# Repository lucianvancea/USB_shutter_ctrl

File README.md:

# Hardware shutter control for astrophotography 

## Intro
* Done in KiCad 
* Tested with [NINA]( https://nighttime-imaging.eu/ ) and Nikon D7000
* Works with this cable [ZWO ASIAIR N3]( https://astronomy-imaging-camera.com/product/zwo-shutter-release-cable-for-asiair-pro )
* [Video of board being soldered]( https://www.youtube.com/watch?v=h37NhTkAf3A&t)
* Uses RTS signal from an USB to UART bridge to control shutter release (and exposure time)

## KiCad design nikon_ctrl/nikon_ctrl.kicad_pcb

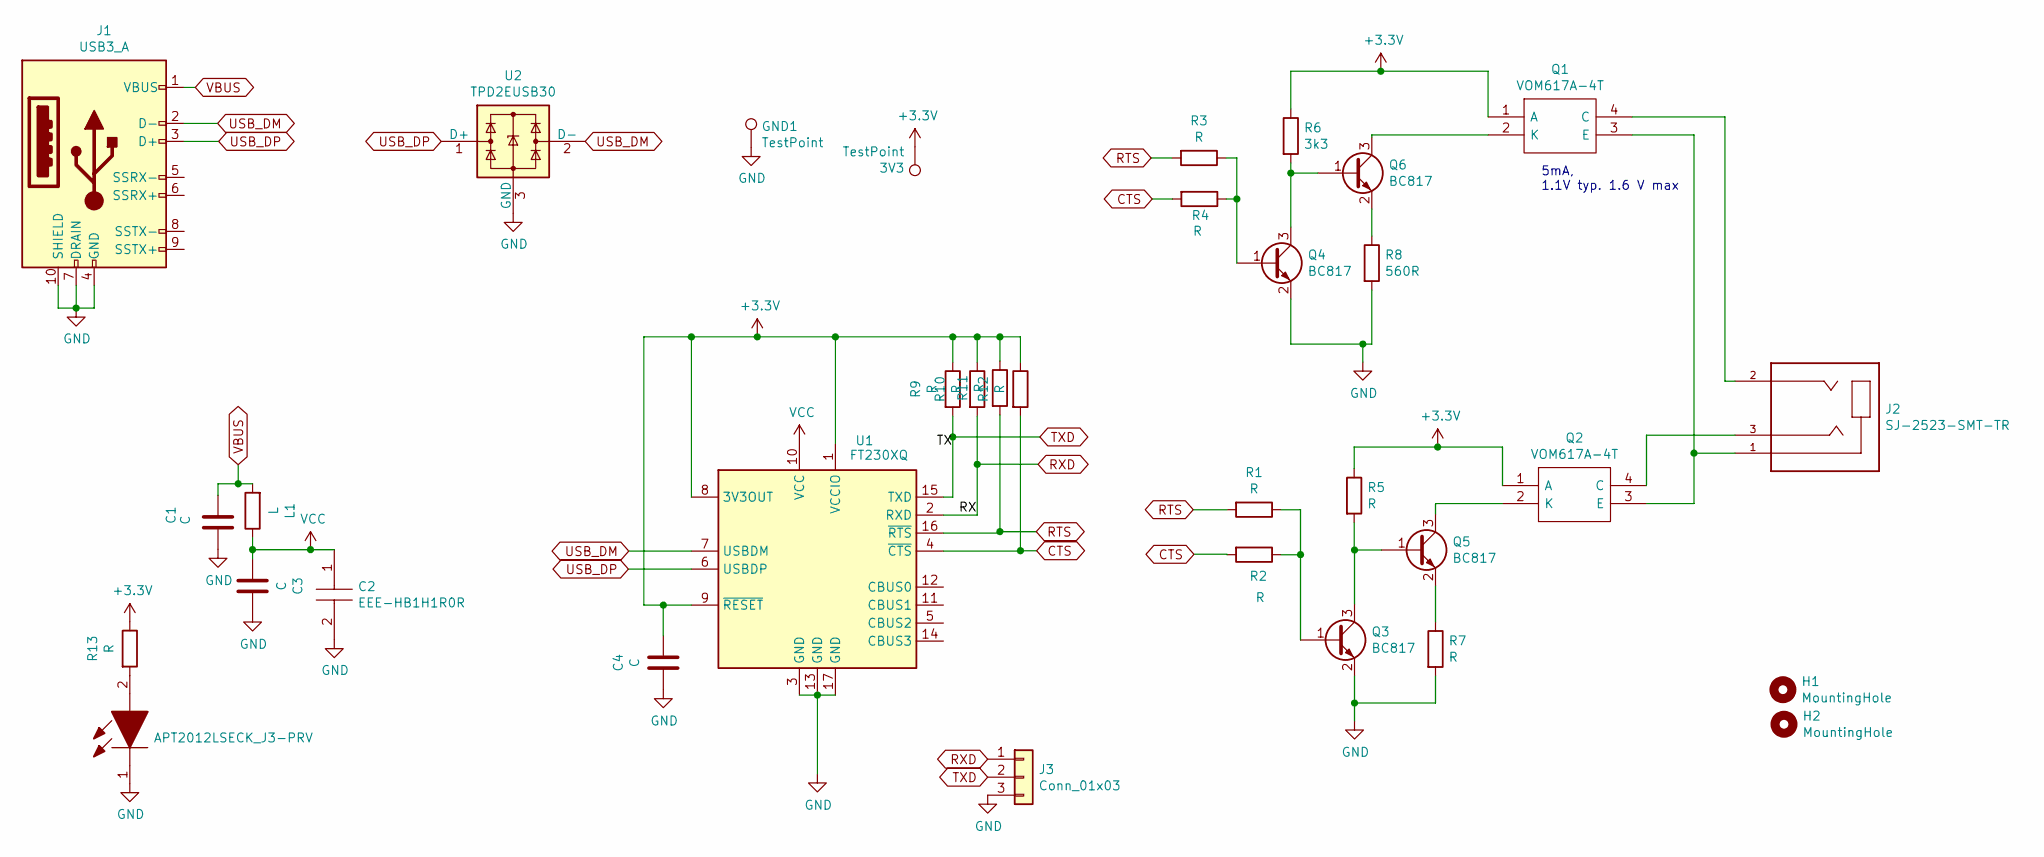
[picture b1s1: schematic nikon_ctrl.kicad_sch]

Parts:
3V3: TestPoint; TestPoint_Pad_D1.5mm
C1, C3, C4: C; C_0805_2012Metric
C2: EEE-HB1H1R0R; CAPAE430X610N; Mouser Part Number 667-EEE-HB1H1R0R
GND1: TestPoint; TestPoint_Pad_D1.5mm
H1, H2: MountingHole; MountingHole_2.2mm_M2_ISO7380_Pad
J1: USB3_A; USB3_A_Plug_Wuerth_692112030100_Horizontal
J2: SJ-2523-SMT-TR; CUI_SJ-2523-SMT-TR
J3: Conn_01x03; PinHeader_1x03_P2.54mm_Vertical
L1: L; R_0805_2012Metric_Pad1.15x1.40mm_HandSolder
LED1: APT2012LSECK_J3-PRV; LEDC2012X75N; Mouser Part Number 604-APT2012LSECKJ3RV
Q1, Q2: VOM617A-4T; VOM617A8X001T; Mouser Part Number 78-VOM617A-4T
Q3, Q4, Q5, Q6: BC817; SOT-23
R1, R2, R3, R4, R5, R7, R9, R10, R11, R12, R13: R; R_0805_2012Metric_Pad1.15x1.40mm_HandSolder
R6: 3k3; R_0805_2012Metric_Pad1.15x1.40mm_HandSolder
R8: 560R; R_0805_2012Metric_Pad1.15x1.40mm_HandSolder
U1: FT230XQ; QFN-16-1EP_4x4mm_P0.65mm_EP2.1x2.1mm
U2: TPD2EUSB30; Texas_DRT-3

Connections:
+3V3: 3V3.1, C4.2, Q1.1 (A), Q2.1 (A), R5.1, R6.1, R9.1, R10.1, R11.1, R12.1, R13.1, U1.1 (VCCIO), U1.8 (3V3OUT), U1.9 (~RESET)
CTS: R2.2, R4.2, R12.2, U1.4 (~CTS)
GND: C1.2, C2.2, C3.2, C4.1, GND1.1, J1.4 (GND), J1.7 (DRAIN), J1.10 (SHIELD), J3.3, LED1.1, Q3.2 (E), Q4.2 (E), R7.2, R8.2, U1.3 (GND), U1.13 (GND), U1.17 (GND), U2.3 (GND)
unnamed: J2.1, Q1.3 (E), Q2.3 (E)
unnamed: J2.2, Q1.4 (C)
unnamed: J2.3, Q2.4 (C)
unnamed: LED1.2, R13.2
unnamed: Q1.2 (K), Q6.3 (C)
unnamed: Q2.2 (K), Q5.3 (C)
unnamed: Q3.1 (B), R1.1, R2.1
unnamed: Q3.3 (C), Q5.1 (B), R5.2
unnamed: Q4.1 (B), R3.1, R4.1
unnamed: Q4.3 (C), Q6.1 (B), R6.2
unnamed: Q5.2 (E), R7.1
unnamed: Q6.2 (E), R8.1
RTS: R1.2, R3.2, R11.2, U1.16 (~RTS)
RXD: J3.1, R10.2, U1.2 (RXD)
TXD: J3.2, R9.2, U1.15 (TXD)
USB_DM: J1.2 (D-), U1.7 (USBDM), U2.2 (D-)
USB_DP: J1.3 (D+), U1.6 (USBDP), U2.1 (D+)
VBUS: C1.1, J1.1 (VBUS), L1.2
VCC: C2.1, C3.1, L1.1, U1.10 (VCC)

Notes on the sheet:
5mA, 1.1V typ. 1.6 V max

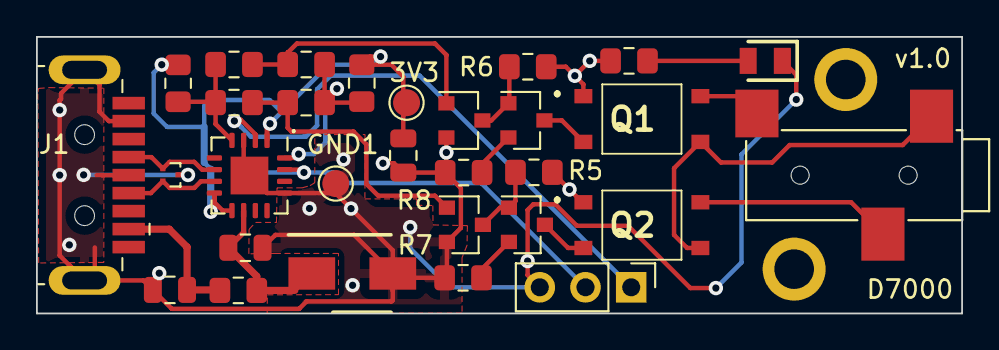
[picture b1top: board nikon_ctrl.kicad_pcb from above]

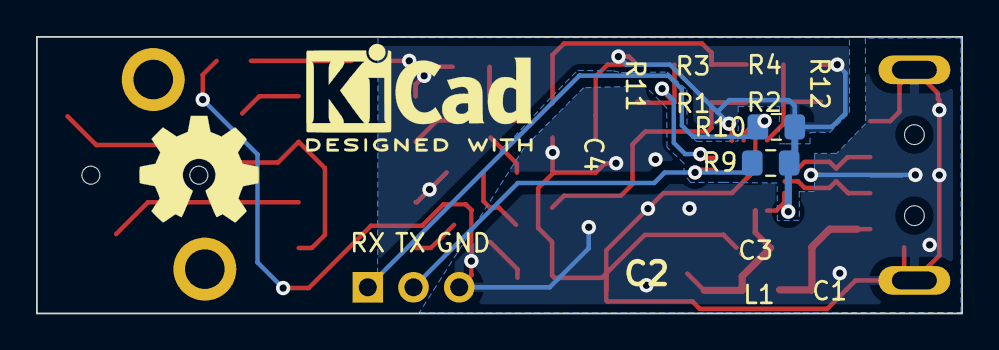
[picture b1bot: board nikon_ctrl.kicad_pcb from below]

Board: 2 copper layers, 51.4 x 15.4 mm, 34 parts (2 on the bottom side), 22 nets.

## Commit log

2021-06-03 adding output for V1.0
2021-06-03 adding Readme file
2021-06-03 adding License
2021-06-03 adding top image
2021-06-03 adding kicad files
2021-06-12 updated component values
